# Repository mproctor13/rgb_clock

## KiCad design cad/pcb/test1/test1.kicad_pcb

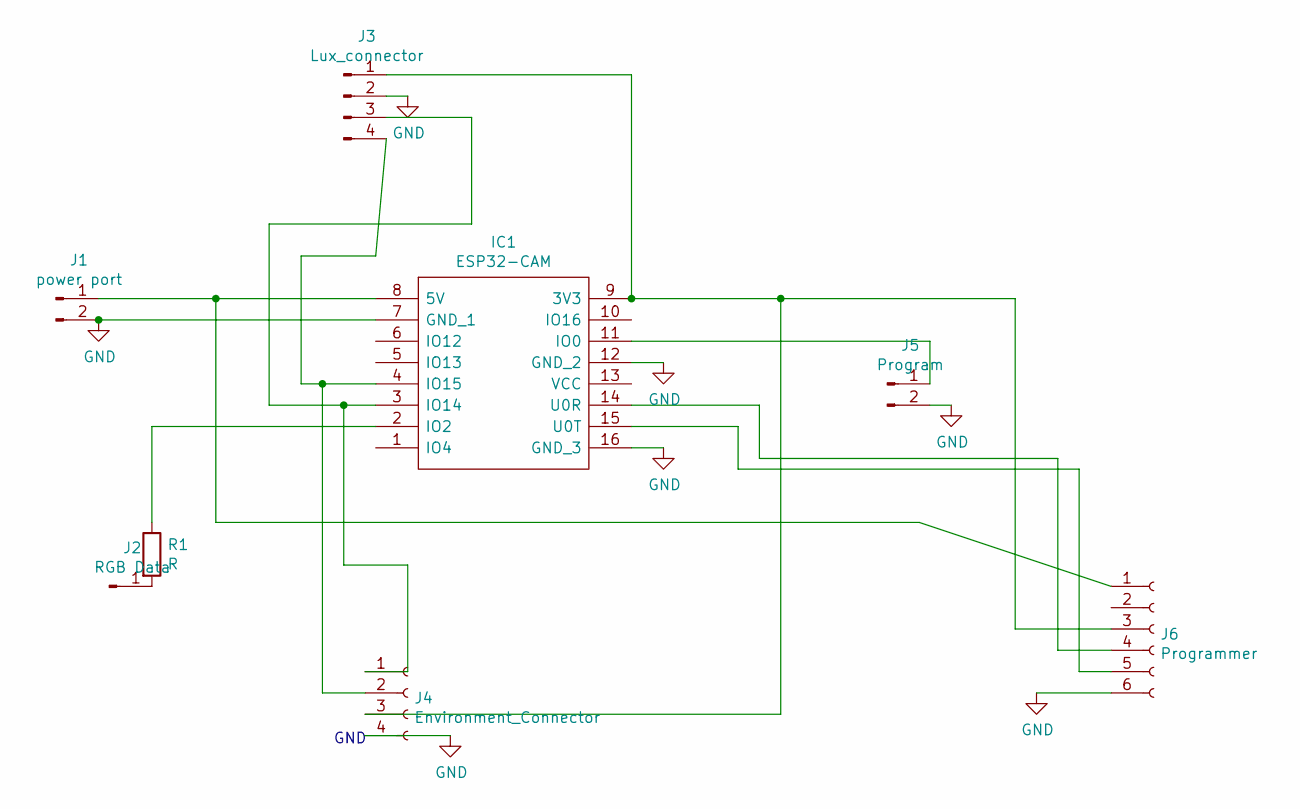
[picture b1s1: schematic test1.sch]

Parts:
IC1: ESP32-CAM; ESP32CAM; Manufacturer_Part_Number ESP32-CAM
J1: power port; PinHeader_1x02_P2.54mm_Vertical
J2: RGB Data; PinHeader_1x01_P2.54mm_Vertical
J3: Lux_connector; PinHeader_1x04_P2.54mm_Vertical
J4: Environment_Connector; PinSocket_1x04_P2.54mm_Vertical
J5: Program; PinHeader_1x02_P2.54mm_Vertical
J6: Programmer; PinSocket_1x06_P2.54mm_Vertical
R1: R; R_Axial_DIN0207_L6.3mm_D2.5mm_P2.54mm_Vertical

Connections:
GND: IC1.7 (GND_1), IC1.12 (GND_2), IC1.16 (GND_3), J1.2, J3.2, J4.4, J5.2, J6.6
unnamed: IC1.2 (IO2), R1.1
unnamed: IC1.3 (IO14), J3.3, J4.1
unnamed: IC1.4 (IO15), J3.4, J4.2
unnamed: IC1.8 (5V), J1.1, J6.1
unnamed: IC1.9 (3V3), J3.1, J4.3, J6.3
unnamed: IC1.11 (IO0), J5.1
unnamed: IC1.14 (U0R), J6.4
unnamed: IC1.15 (U0T), J6.5
unnamed: J2.1, R1.2

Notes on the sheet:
GND

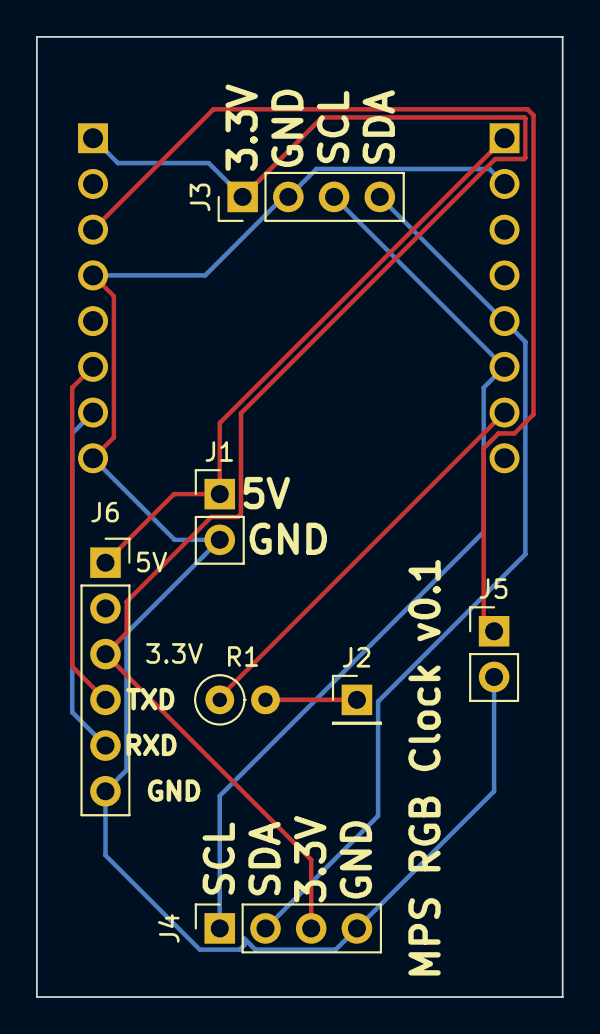
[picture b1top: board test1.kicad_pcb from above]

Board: 2 copper layers, 29.2 x 53.3 mm, 8 parts (1 on the bottom side), 10 nets.

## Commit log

2021-01-02 initial nsl code
2021-01-02 Add open close urls
2021-01-02 set nsl name
2021-01-03 deployed version
2021-01-16 disable brownout detector
2021-11-08 fix json
2021-11-09 convert to platform.io
2021-11-09 kicad board to drive cloc
2024-07-09 Current found 07/09/24
